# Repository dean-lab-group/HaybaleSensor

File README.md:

# Haybale Sensor App
> An app for managing sensors that go into Haybales and alerts farmers when conditions for ignition exist.

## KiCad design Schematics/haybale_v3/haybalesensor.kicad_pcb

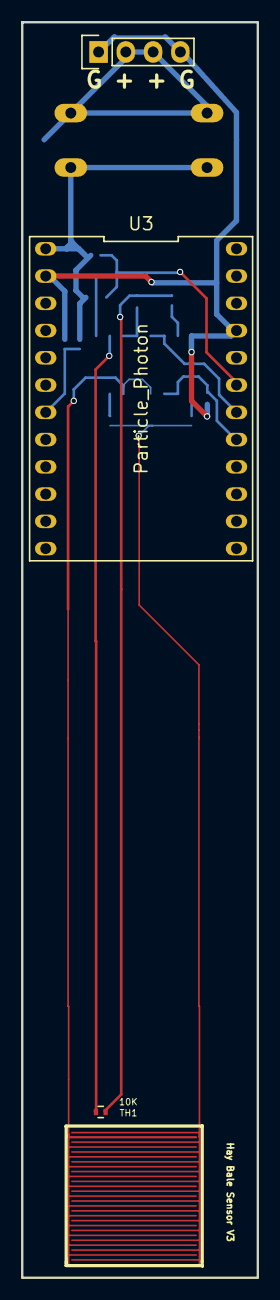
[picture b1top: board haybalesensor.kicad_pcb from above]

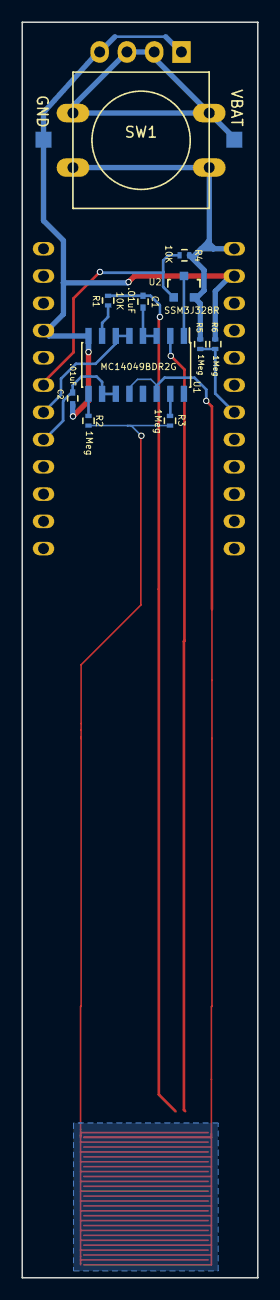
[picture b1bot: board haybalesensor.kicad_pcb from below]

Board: 4 copper layers, 21.9 x 117.0 mm, 16 parts (13 on the bottom side), 16 nets.

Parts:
C1, C2: .01uF; C_0402
P2: VBAT; Measurement_Point_Square-SMD-Pad_Small
P3: GND; Measurement_Point_Square-SMD-Pad_Small
P5: CONN_01X04; Pin_Header_Straight_1x04
R1, R4: 10K; R_0402
R2, R3, R5, R6: 1Meg; R_0402
SW1: SPST; SW_PUSH-12mm
TH1: 10K; R_0402
U1: MC14049BDR2G; SOIC-16_3.9x9.9mm_Pitch1.27mm
U2: SSM3J328R; SOT-23
U3: Particle_Photon; Particle-Photon

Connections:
/Cap1: U1.12, U1.14
/Cap2: R2.2, R3.2
GND: C2.1, P3.1, P5.1, P5.4, R6.2, U1.8, U3.2, U3.21
unnamed: C1.1, U1.3, U1.4
unnamed: C1.2, R1.2, TH1.2
unnamed: C2.2, U1.10, U1.11, U3.17
unnamed: P2.1, P5.2, P5.3, SW1.1
unnamed: R1.1, U1.7
unnamed: R2.1, U1.9
unnamed: R3.1, U1.15
unnamed: R4.1, U2.1, U3.19
unnamed: R5.1, R6.1, U3.7
unnamed: TH1.1, U1.2
unnamed: U1.1, U2.3
unnamed: U1.5, U1.6, U3.18
VDD: R4.2, R5.2, SW1.2, U2.2, U3.1

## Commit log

2016-09-19 Working hourly update
2016-09-19 Final commit + logs for sept19
2016-09-20 Updated logs, added TODO.txt, commented haybalev01.ino
2016-09-23 added comments and code for 5min updates; currently set for 1 minute publishing
2016-09-27 Enabled CTRL line and sleep modes
2016-10-05 Control flow operating correctly
2016-10-12 Persistent Internet Version
2016-10-18 Added Wi-Fi connection checks
2016-10-19 Changed 15 minute sleep time to be more accurate
2016-11-08 Updated comments
2017-02-23 1) Program for linearly interpolating sensor data for each sersor. 2) Soft Access Point work. 3) Sensor data that was collected.
2017-02-23 Added images for Jeff.
2017-04-10 Fixed Fifteen minute delay; added .gitignore
2017-04-10 Removed logs from repository
2017-05-22 Uploaded Data from Field Test
    Test Data May 2017
2017-05-22 Added program to calibrate new boards.
2017-05-22 Updated to work with new sensors and new calibration graphs
2017-05-22 Cleanup and moved sensor data to its own folder.
2017-05-22 Added calibration to sensor data.
2017-08-15 What is this?
2017-08-15 This is my latest haybale sensor code.
2017-08-16 Added some data from Jeff. Waiting on the rest of it.
2017-08-17 Adding Jeff's calibration stuff
2017-08-17 Clean up files
2017-08-18 Latest code. I cleaned up everything and made it functions.
2017-08-24 Latest updates.
    * Added Calibration Manager class that converts calibration data from
    cloud to EEPROM.
    * Added convert.{cpp|h} to convert using Jeff's method.
2017-10-04 Latest changes
    Added code to calibrate sensors.
    Added a python script to read serial ports and create csv output.
2017-10-05 Added calibration program and some more tweaks to the haybale code.
2017-10-13 Latest changes. Finished JS to serve temp page.
2017-10-13 C++ Code Changes
2018-02-05 Latest changes. Finished JS to serve temp page. Next step: Move to Particle stack.
2018-02-23 Major cleanup and reorg. All code that used to be in one project has been separated into separate C++ libraries.
2018-02-24 Working softap code. Will re-enable formatting sensor values. Whenever I do, I get a heap error...
2018-02-24 SoftAP code complete. Need to update with calibration manager next.
2018-03-01 Reorg
2018-07-16 Updated for Auburn Data Collection
2018-07-16 Added new project called AuburnBales for Dept of Ag data collection.
2018-07-16 Added schematics and few cleanups.
2018-07-16 Final Hay Bale Code.
2018-07-18 Final checkin
